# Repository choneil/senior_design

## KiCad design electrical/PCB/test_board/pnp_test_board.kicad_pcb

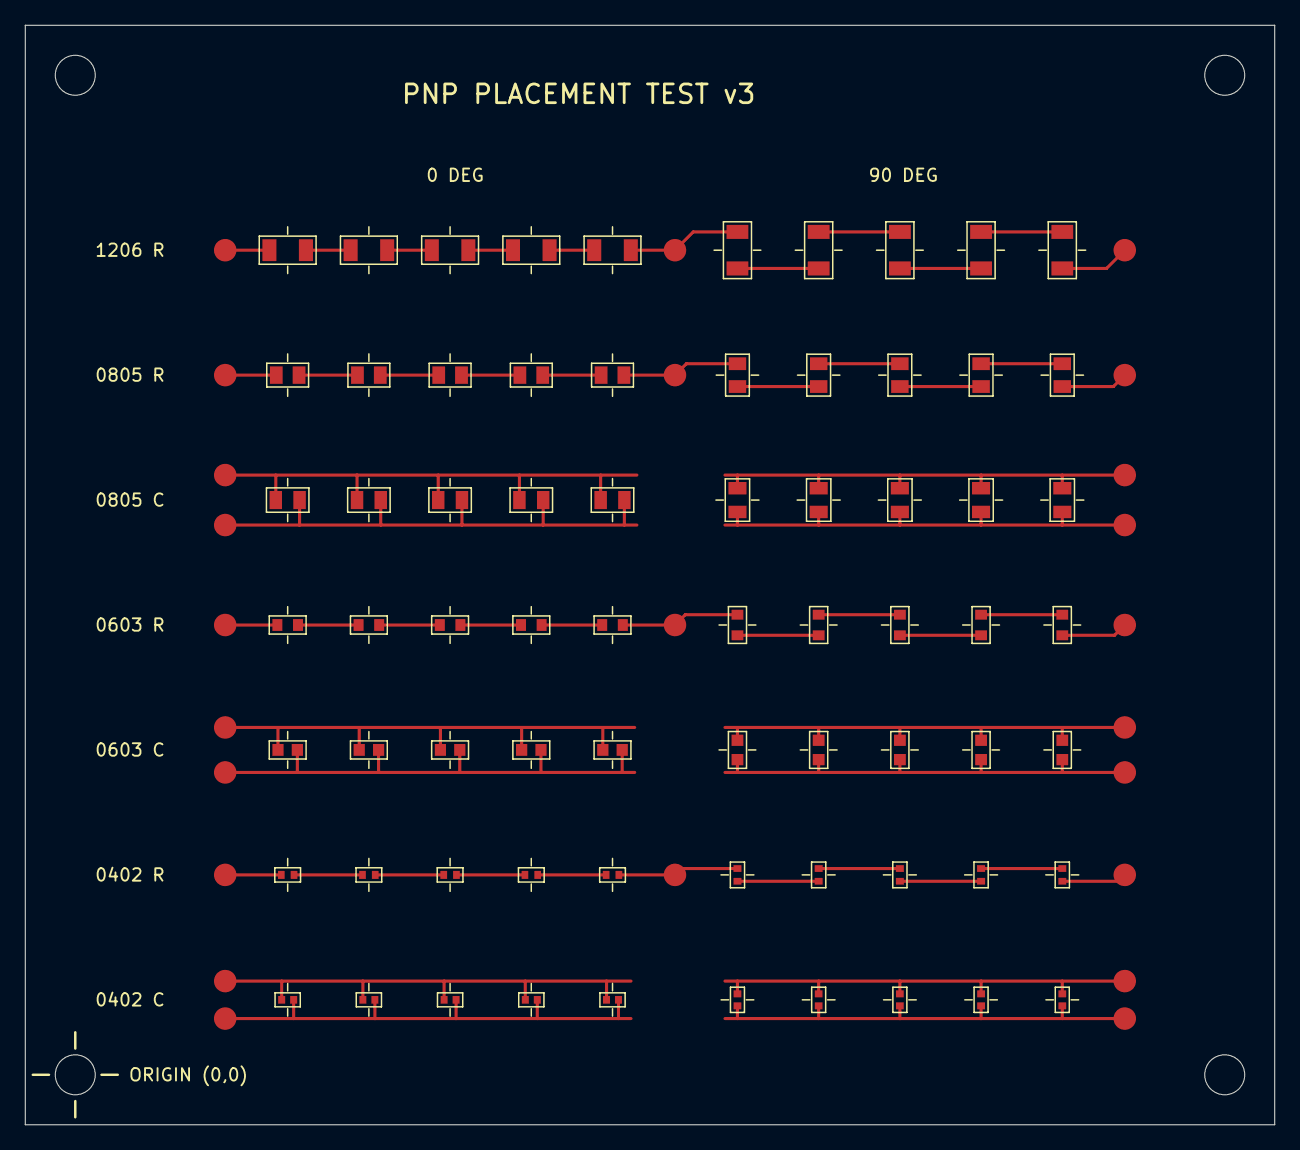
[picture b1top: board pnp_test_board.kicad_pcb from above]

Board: 2 copper layers, 100.0 x 88.0 mm, 98 parts (0 on the bottom side), 56 nets.

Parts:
C1, C2, C3, C4, C5, C6, C7, C8, C9, C10: 100nF; C_0805_2012Metric
C11, C12, C13, C14, C15, C16, C17, C18, C19, C20: 100nF; C_0603_1608Metric
C21, C22, C23, C24, C25, C26, C27, C28, C29, C30: 100nF; C_0402_1005Metric
H1, H2, H3, H4: M3; MountingHole_3.2mm_M3
R1, R2, R3, R4, R5, R6, R7, R8, R9, R10: 1k; R_1206_3216Metric
R11, R12, R13, R14, R15, R16, R17, R18, R19, R20: 1k; R_0805_2012Metric
R21, R22, R23, R24, R25, R26, R27, R28, R29, R30: 1k; R_0603_1608Metric
R31, R32, R33, R34, R35, R36, R37, R38, R39, R40: 1k; R_0402_1005Metric
TP1, TP2, TP3, TP4, TP5, TP6, TP7, TP8, TP9, TP10, TP11, TP12, TP13, TP14, TP15, TP16, TP17, TP18, TP19, TP20, TP21, TP22, TP23, TP24: TP; TestPoint_Pad_D1.8mm

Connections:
C0402_L_A: C21.1, C22.1, C23.1, C24.1, C25.1, TP21.1
C0402_L_B: C21.2, C22.2, C23.2, C24.2, C25.2, TP22.1
C0402_R_A: C26.2, C27.2, C28.2, C29.2, C30.2, TP23.1
C0402_R_B: C26.1, C27.1, C28.1, C29.1, C30.1, TP24.1
C0603_L_A: C11.1, C12.1, C13.1, C14.1, C15.1, TP14.1
C0603_L_B: C11.2, C12.2, C13.2, C14.2, C15.2, TP15.1
C0603_R_A: C16.2, C17.2, C18.2, C19.2, C20.2, TP16.1
C0603_R_B: C16.1, C17.1, C18.1, C19.1, C20.1, TP17.1
C0805_L_A: C1.1, C2.1, C3.1, C4.1, C5.1, TP7.1
C0805_L_B: C1.2, C2.2, C3.2, C4.2, C5.2, TP8.1
C0805_R_A: C6.2, C7.2, C8.2, C9.2, C10.2, TP9.1
C0805_R_B: C6.1, C7.1, C8.1, C9.1, C10.1, TP10.1
R0402_N0: R31.1, TP18.1
R0402_N1: R31.2, R32.1
R0402_N2: R32.2, R33.1
R0402_N3: R33.2, R34.1
R0402_N4: R34.2, R35.1
R0402_N5: R35.2, R36.2, TP19.1
R0402_N6: R36.1, R37.1
R0402_N7: R37.2, R38.2
R0402_N8: R38.1, R39.1
R0402_N9: R39.2, R40.2
R0402_N10: R40.1, TP20.1
R0603_N0: R21.1, TP11.1
R0603_N1: R21.2, R22.1
R0603_N2: R22.2, R23.1
R0603_N3: R23.2, R24.1
R0603_N4: R24.2, R25.1
R0603_N5: R25.2, R26.2, TP12.1
R0603_N6: R26.1, R27.1
R0603_N7: R27.2, R28.2
R0603_N8: R28.1, R29.1
R0603_N9: R29.2, R30.2
R0603_N10: R30.1, TP13.1
R0805_N0: R11.1, TP4.1
R0805_N1: R11.2, R12.1
R0805_N2: R12.2, R13.1
R0805_N3: R13.2, R14.1
R0805_N4: R14.2, R15.1
R0805_N5: R15.2, R16.2, TP5.1
R0805_N6: R16.1, R17.1
R0805_N7: R17.2, R18.2
R0805_N8: R18.1, R19.1
R0805_N9: R19.2, R20.2
R0805_N10: R20.1, TP6.1
R1206_N0: R1.1, TP1.1
R1206_N1: R1.2, R2.1
R1206_N2: R2.2, R3.1
R1206_N3: R3.2, R4.1
R1206_N4: R4.2, R5.1
R1206_N5: R5.2, R6.2, TP2.1
R1206_N6: R6.1, R7.1
R1206_N7: R7.2, R8.2
R1206_N8: R8.1, R9.1
R1206_N9: R9.2, R10.2
R1206_N10: R10.1, TP3.1

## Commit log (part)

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2026-04-06 Fix: enable scroll
2026-04-06 scroll
2026-04-06 scroll again
2026-04-06 scroll in chart container
2026-04-06 scroll with wheel
2026-04-06 fix height
2026-04-06 fix scroll
2026-04-06 fix scroll gotta be right fr now
2026-04-06 event listener in script js for scrollwheel
2026-04-06 all in one
2026-04-06 Remove Gantt chart implementation
    Removed the entire Gantt chart implementation from script.js, including timeline variables, event listeners, and series data.
2026-04-06 Remove styles from styles.css
    Removed global styles and specific component styles for header and controls.
2026-04-06 remove .js and .css files. merge to html
2026-04-06 fix timeline
2026-04-06 fix task blurb scaling with dates
2026-04-08 csv schedules
2026-04-08 populate from csvs
2026-04-08 remove local file upload
2026-04-08 Update TBD to 'Draft prototype' in schedule
2026-04-13 Revise gantry system schedule with detailed tasks
    Updated the gantry system schedule with specific tasks and deadlines.
2026-04-13 Combine tasks in gantry_system.csv for clarity
2026-04-22 inventory csvs
2026-04-22 added rambo board schematics
2026-04-22 made folders in rambo dir
2026-04-22 moved rambov1.2 into documentation folder.
2026-04-22 removed rambov1.2 from main folder
2026-04-22 adding test code for motors
2026-04-22 Create Spending
2026-04-22 Created receipts file
2026-04-27 Update schedule for 2026-05-04 with Chuck-MUX details
2026-04-27 Update solder dispensing schedule entries
2026-05-01 decomposition/definition of most of the systems, organization of some tasks to be done
2026-05-01 readme for decomposition
2026-05-01 latex report files
2026-05-01 updated image quality in report pngs
2026-05-01 title fix
2026-05-01 decomp titles and captions fix
2026-05-07 Vacuum Head rotation and z-axis parts
    Added details about Z-axis stepper motor and components.
2026-05-07 Update stepper_control.txt with Z-axis movement details
    Clarified definition of Z-axis movement for the vacuum head and added details about the stepper motor configuration.
2026-05-29 Marlin Firmware configuration for Rambo Board using 128x64 i2c OLEDs.
2026-06-21 Added Feeder BOM
2026-06-21 changed feeder BOM to CSV file
2026-06-21 Create feeder
